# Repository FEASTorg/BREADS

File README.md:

# BREADS

BREADS is the Broadly Expandable and Reconfigurable Data Acquisition and Automation Device Standard.

> You’ve heard of breaking bread — now try building with it!

## Documentation

To see the full documentation visit [our page](https://feastorg.github.io/BREADS/).

## Contributing

Start designing your own slice or make a pull with your improvements!

For more details see the [feastorg CONTRIBUTING](https://github.com/feastorg/.github/blob/main/profile/CONTRIBUTING.md) guidelines on our organization profile.

### Mechanical (Cases)

All case designs can be found on [Onshape](https://cad.onshape.com/documents/f4c13a5c0b1f8d88ed1f5752/w/29d0c0346ddaeb06e16ff42f/e/1077373224ada363d171e3fe?renderMode=0&uiState=65d3aad45b82c32cb51ae4c9)

### Ideas

To see the current wish list for the BREADS family see the [bread ideas](docs/dev_docs/future_slice_ideas.md) doc.

## License

All firmware and software in this repository are licensed under the GNU General Public License v3.0 (GPLv3), and all hardware is licensed under the CERN Open Hardware Licence Version 2 – Strongly Reciprocal (CERN OHL-S v2). These licenses apply specifically to all original designs, technologies, and artwork developed for the BREADS project.

See the relevant [license](./LICENSE) file for full terms, including usage, modification, and redistribution.

## Acknowledgements

[Acknowledge any contributors, collaborators, funding sources, or organizations that supported the project.]

## Contact

[Provide contact information for the project maintainer(s) or lead researcher(s). Include an email address or a link to a contact form.]

---

<div align="center">
  
</div>

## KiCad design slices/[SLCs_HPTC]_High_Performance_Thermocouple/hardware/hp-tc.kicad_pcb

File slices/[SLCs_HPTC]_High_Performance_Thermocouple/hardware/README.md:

# High Performance Thermocouple Amplifier

## Design Goals and Specifications for High-Speed Isolated Thermocouple Project

### Calibration and Temperature Considerations
- Calibration techniques will rely on physical phenomena, like boiling points, but must account for atmospheric pressure variations, as these can affect the boiling points. 
    - Particularly relevant for calibration at different elevations above sea level.
- A proposal to use distilled water for calibration to achieve "close enough" results within a +/-0.1°C margin at a 100°C range was discussed but noted to have limitations based on elevation and atmospheric conditions.
- An alternative calibration method involving triple-point thermal references was suggested for precision but recognized as less accessible.

### Thermocouple and Amplifier Specifications
- The project will initially focus on Type K thermocouples.
- The analog front-end amplifier should have an input-offset less than 4μV. Noise, drift, and linearity, along with not loading the thermocouple, are primary concerns.
- The aim is for the thermocouple to have no more than 10 microamps of loading current, preferably less than 1.5 microamps.
- Microcontroller Unit (MCU) specifications include at least 16KB flash to accommodate future expansions like a Look-Up Table (LUT) for better matching to the exact thermocouple curve.

### Design and Integration
- The discussion covered different approaches to integrating the components, emphasizing the importance of a high input impedance for accurate measurements.
- A digital temperature sensor for ambient temperature measurement at the thermocouple connection point on the board was considered crucial for relative measurements.
- There was a significant focus on selecting the right connectors and ensuring compatibility with different thermocouples, as well as considering built-in cold-compensation sensors.

### Component Selection and Cost Considerations
- Efforts to minimize costs while maintaining performance were evident, with discussions around sourcing components, choosing MCUs with built-in DACs, and finding economical PCB manufacturing options.
- The Bill of Materials (BOM) cost estimation hovered around $25-$30, with additional costs for PCB manufacturing and shipping considered. The aim is to keep the total cost reasonable while enabling scalability in manufacturing.

### Calibration and Output Accuracy
- There were suggestions for making the linear approximation of temperature readings accurate within specific high-temperature ranges (900°C to 1100°C), acknowledging that errors at lower temperatures would be less critical.
- Digital outputs and possibly eliminating analog outputs were discussed to streamline the design and reduce complexity.

### PCB Design and Manufacturing
- Advanced PCB design techniques were considered to accommodate tight space requirements and high-resolution traces, specifically for components like QFN packages with exposed pads.
- The possibility of integrating a designated type K thermocouple socket was discussed, noting its impact on the BOM cost but its importance for compatibility and ease of use.

### Additional Notes
- The team explored various ideas for enhancing the project's design, such as integrating temperature sensors directly on the PCB for more accurate cold-junction compensation and discussing the practical aspects of assembling small components without professional equipment.
- There was a continuous emphasis on balancing performance, cost, and usability to ensure that the final product would be accessible and useful to a broad audience.

## Technical Dissemination

### 1. Power Supply and Isolation

#### Components:
- **U3 (H11L1)**: Optocoupler
- **U4, U5 (AP2112K-3.3)**:  3.3V low dropout regulators. Provide isolated stable voltage for the circuit.
- **D1 (Schottky Diode)**: Reverse polarity protection.
- **L1 (Coupled Inductor)**: Provides isolation and filtering for the power supply.
- **C1, C2, C3, C4, C5, C6, C7, C8, C9, C10, C11, C12**: Capacitors for filtering and decoupling.
- **D2 (Zener Diode)**: Overvoltage protection.
- **R1, R2, R3, R4**: Current limiting and voltage division resistors.

### 2. Thermocouple Input and Amplification

#### Components:
- **U6A (IS1221)**: Instrumentation amplifier for thermocouple signal amplification.
- **R5, R6, R7**: Precision resistors for setting amplifier gain.
- **C13, C14, C15, C16, C17, C18, C19**: Filtering capacitors.
- **R8 (Trim-Pot)**: Adjustable resistor for fine-tuning gain.

### 3. Analog-to-Digital Conversion

#### Components:
- **U7 (MCP1501T-20E)**: Precision voltage reference.
- **U2 (MCP3565R)**: High-resolution ADC.
- **C20, C21, C22, C23, C24, C25, C26, C27, C28, C29, C30**: Decoupling and filtering capacitors.
- **R9, R10, R11, R12, R13, R14, R15, R16, R17**: Resistors for setting input impedance and filtering.

### 4. Microcontroller and Interface

### Components:
- **U1 (MSPM0G1507SPTR)**: Microcontroller for processing digital signals and handling communication.
- **C31, C32, C33, C34, C35, C36**: Decoupling capacitors for MCU power supply.
- **R18, R19, R20**: Resistors for setting up MCU I/O lines.

### 5. Temperature Sensor for Cold-Junction Compensation

#### Components:
- **U10 (TMP112)**: Digital temperature sensor.
- **R21, R22**: Pull-up resistors for I2C lines.
- **C37, C38**: Decoupling capacitors.

### 6. Isolation and Data Communication

#### Components:
- **ISO-MISO, ISO-MOSI**: Isolated SPI lines.
- **ISO6721RB**: Digital isolator.
- **C39, C40, C41**: Filtering capacitors.

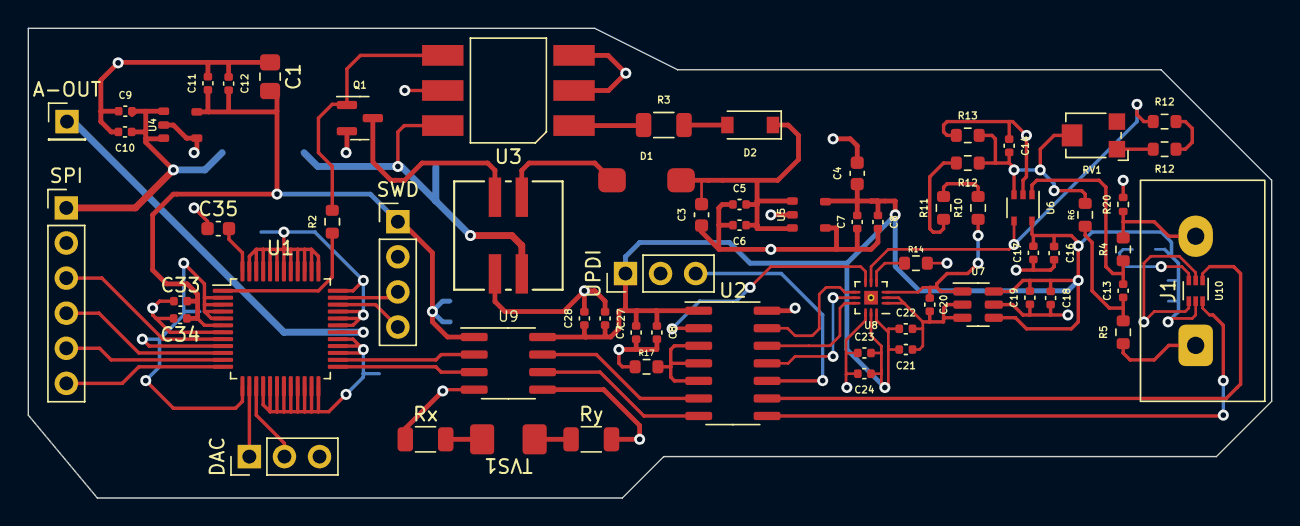
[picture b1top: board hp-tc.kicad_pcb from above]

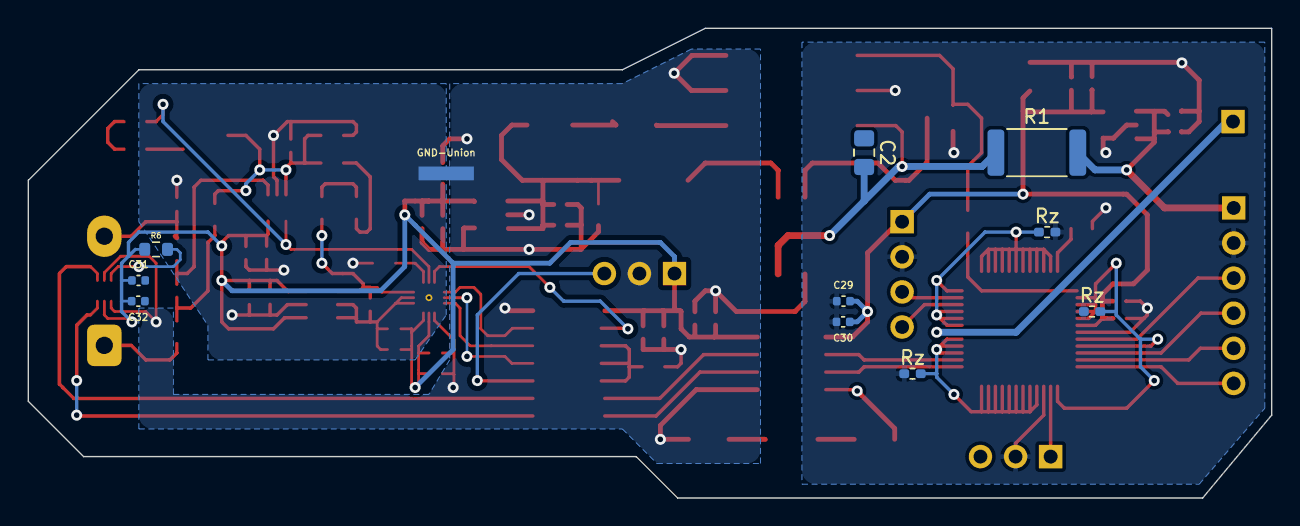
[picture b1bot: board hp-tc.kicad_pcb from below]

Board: 2 copper layers, 90.0 x 34.0 mm, 78 parts (11 on the bottom side), 4 nets.

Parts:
A-OUT: PinHeader_1x01_P2.54mm_Vertical
C1, C2: C_0805_2012Metric_Pad1.18x1.45mm_HandSolder
C3, C4: 2u2; C_0603_1608Metric
C5, C7, C7#2, C9, C11, C14, C16, C18, C20, C21, C23, C27, C29, C31, C33: 1u; C_0402_1005Metric
C6, C8, C8#2, C10, C12, C17, C19, C22, C24, C28, C30, C32, C34: 10n; C_0402_1005Metric
C13: 0u1; C_0402_1005Metric
C35: 0u47; C_0603_1608Metric
D1: SK14
D2: 3v; D_SOD-123
DAC: PinHeader_1x03_P2.54mm_Vertical
GND-Union: GND-Union
J1: TypeKSocket
L1: SRF0703-6R8M; IND_SRF0703-101M_BRN-M
Q1: DMN2310U; SOT-23
R1: 4R7; R_2512_6332Metric
R2: 1K; R_0603_1608Metric
R3: 10; R_1206_3216Metric
R4, R5, R10, R11, R12, R13: 1k; R_0603_1608Metric
R6, R6#2, R14, R17: 22k; R_0603_1608Metric
R12#2: 47k; R_0603_1608Metric
R12#3: 470k; R_0603_1608Metric
R20: 10M; R_0402_1005Metric
RV1: 20k; Potentiometer_Bourns_TC33X_Vertical
Rx: R_1206_3216Metric
Ry: R_1206_3216Metric
Rz: 1M; R_0402_1005Metric_Pad0.72x0.64mm_HandSolder
Rz#2, Rz#3: 1M; R_0402_1005Metric_Pad0.72x0.64mm_HandSolder
SPI: PinHeader_1x06_P2.54mm_Vertical
SWD: PinHeader_1x04_P2.54mm_Vertical
TVS1: DO-214AA
U1: MSPM0G1507SPTR; LQFP-48_7x7mm_P0.5mm
U2: ATtiny1604; SOIC-14_3.9x8.7mm_P1.27mm
U3: H11L1; H11L1-4
U4, U5: SOT25
U6: TSZ121; SOT-353_SC-70-5
U7: MCP1501; SOT-23-6
U8: MCP3565
U9: ISO6721RFBDR; SOIC-8_3.9x4.9mm_P1.27mm
U10: TMP112; SOT-563
UPDI: PinHeader_1x03_P2.54mm_Vertical

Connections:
GND1: C1.1, C9.1, C10.2, C11.2, C12.1, C29.1, C30.2, C33.1, C34.2, C35.1, DAC.2, Q1.2, Rz.1, Rz#2.1, Rz#3.2, SPI.2, SWD.2, U1.7, U3.5, U4.2, U4.4
GND2: C3.1, C4.2, C5.1, C6.2, C7.1, C7#2.1, C8.2, C8#2.2, C23.1, C24.2, C27.1, C28.2, C31.2, C32.1, GND-Union.1, L1.4, R17.1, Ry.2, U2.14, U3.2, U3.3, U5.2, U5.4, U8.10, U9.5, U10.2, U10.4, UPDI.2
GNDA: C14.1, C16.2, C17.1, C18.2, C19.1, C20.2, C21.1, C22.2, GND-Union.2, R13.1, R14.2, R20.2, U6.2, U7.2, U7.3, U7.5, U8.1, U8.2, U8.13
UPDI: U2.10, UPDI.3

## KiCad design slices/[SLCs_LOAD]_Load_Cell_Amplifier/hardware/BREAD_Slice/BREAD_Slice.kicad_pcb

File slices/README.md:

# slices

## Directory Contents

- Management
  - [LOAFm_ESPTP_ESP32_Thing_Plus_Controller](./[LOAFm_ESPTP]_ESP32_Thing_Plus_Controller/README.md)
  - [LOAFm_x04_LOAF_Backplane_Extender_x04](./[LOAFm_x04]_LOAF_Backplane_Extender_x04/README.md)
- Actuation
  - [SLCa_SERV_Servo_Motor_Controller](./[SLCa_SERV]_Servo_Motor_Controller/README.md)
  - [SLCa_STEP_Stepper_Motor_Controller](./[SLCa_STEP]_Stepper_Motor_Controller/README.md)
  - [SLCa_DCMT_DC_Motor_Controller](./[SLCa_DCMT]_DC_Motor_Controller/README.md)
  - [SLCa_PUMP_Pump_Controller](./[SLCa_PUMP]_Pump_Controller/README.md)
  - [SLCa_RLAY_4_Channel_Relay](./[SLCa_RLAY]_4_Channel_Relay/README.md)
  - [SLCa_DC_Motor_Discrete_HBridge](./[SLCa_DCMT]_DC_Motor_Discrete_HBridge/README.md) **New**
- Communication
  - [SLCc_USBP_USB_Port](./[SLCc_USBP]_USB_Port/README.md)
- Integrated
  - [SLCi_HEAT_Heating_Element_Controller](./[SLCi_HEAT]_Heating_Element_Controller/README.md)
  - [SLCi_RLHT_Relay_Heating_Element_Controller](./[SLCi_RLHT]_Relay_Heating_Element_Controller/README.md)
- Power
  - [SLCp_BUCK_Buck_Converter_Signal_Generator](./[SLCp_BUCK]_Buck_Converter_Signal_Generator/README.md)
  - [SLCp_SOLR_Field_Solar_Power](./[SLCp_SOLR]_Field_Solar_Power/README.md)
- Sensing
  - [SLCs_CR40_40A_Current_Sensor](./[SLCs_CR40]_40A_Current_Sensor/README.md)
  - [SLCs_CR20_20A_Current_Sensor](./[SLCs_CR20]_20A_Current_Sensor/README.md)
  - [SLCs_CR10_10A_Current_Sensor](./[SLCs_CR10]_10A_Current_Sensor/README.md)
  - [SLCs_LVAI_Analog_Reader](./[SLCs_LVAI]_Analog_Reader/README.md)
  - [SLCs_AAFT_Audio_Analysis](./[SLCs_AAFT]_Audio_Analysis/README.md)
  - [SLCs_THRM_Thermocouple_Reader](./[SLCs_THRM]_Thermocouple_Reader/README.md)
  - [SLCs_PHDO_pH_Dissolved_Oxygen_Sensor](./[SLCs_PHDO]_pH_Dissolved_Oxygen_Sensor/README.md)
  - [SLCs_PDER_pH_DO_EC_RP_Sensor](./[SLCs_PDER]_pH_DO_EC_RP_Sensor/README.md) **New**
  - [SLCs_HPTC_High_Performance_Thermocouple](./[SLCs_HPTC]_High_Performance_Thermocouple/README.md) **New**
  - [SLCs_LOAD_Load_Cell_Amplifier](./[SLCs_LOAD]_Load_Cell_Amplifier/README.md) **New**
- Template
  - [SLCx_TEMP_Template](./[SLCx_TEMP]_Template/README.md)

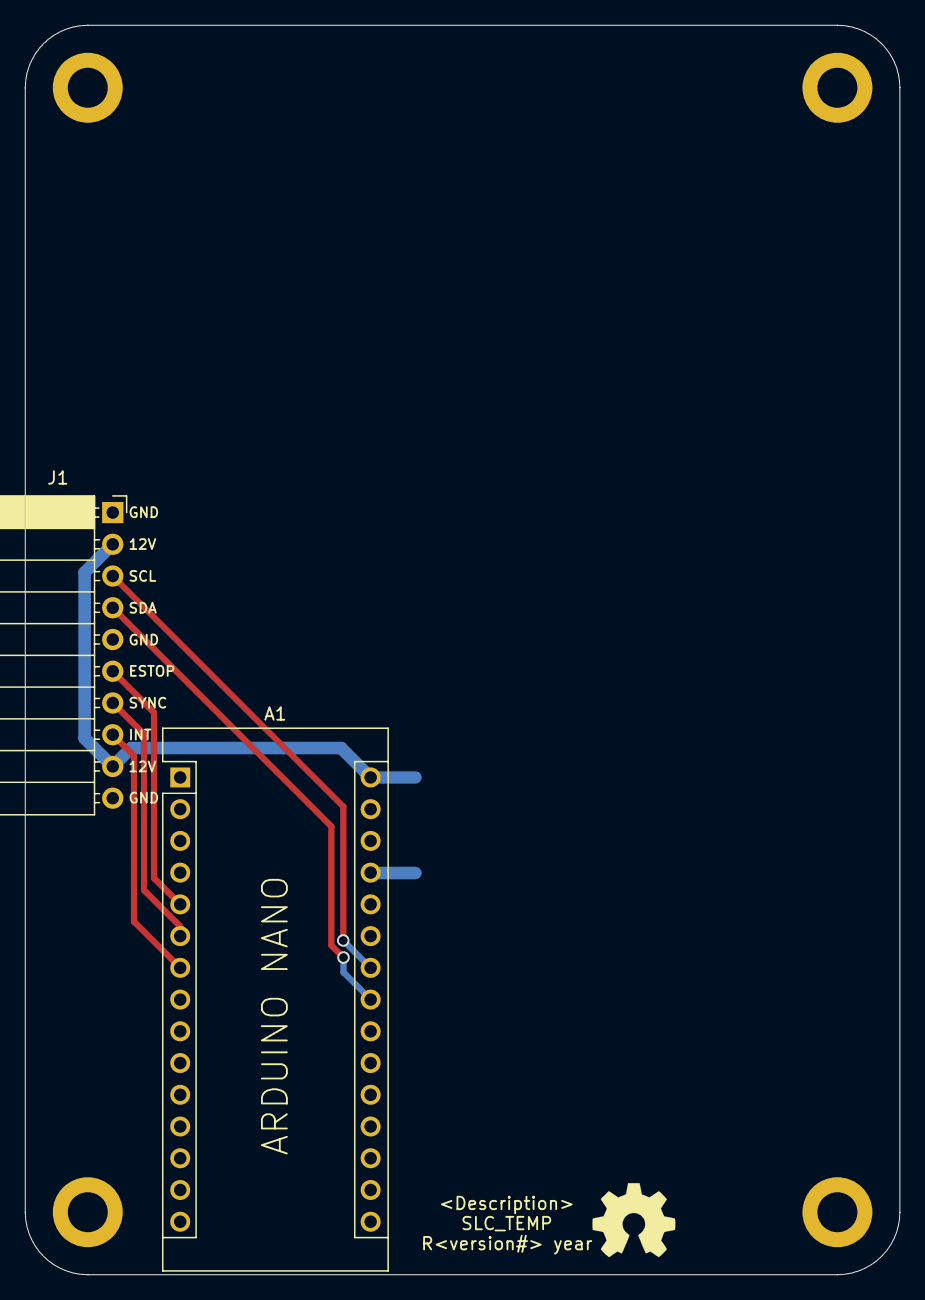
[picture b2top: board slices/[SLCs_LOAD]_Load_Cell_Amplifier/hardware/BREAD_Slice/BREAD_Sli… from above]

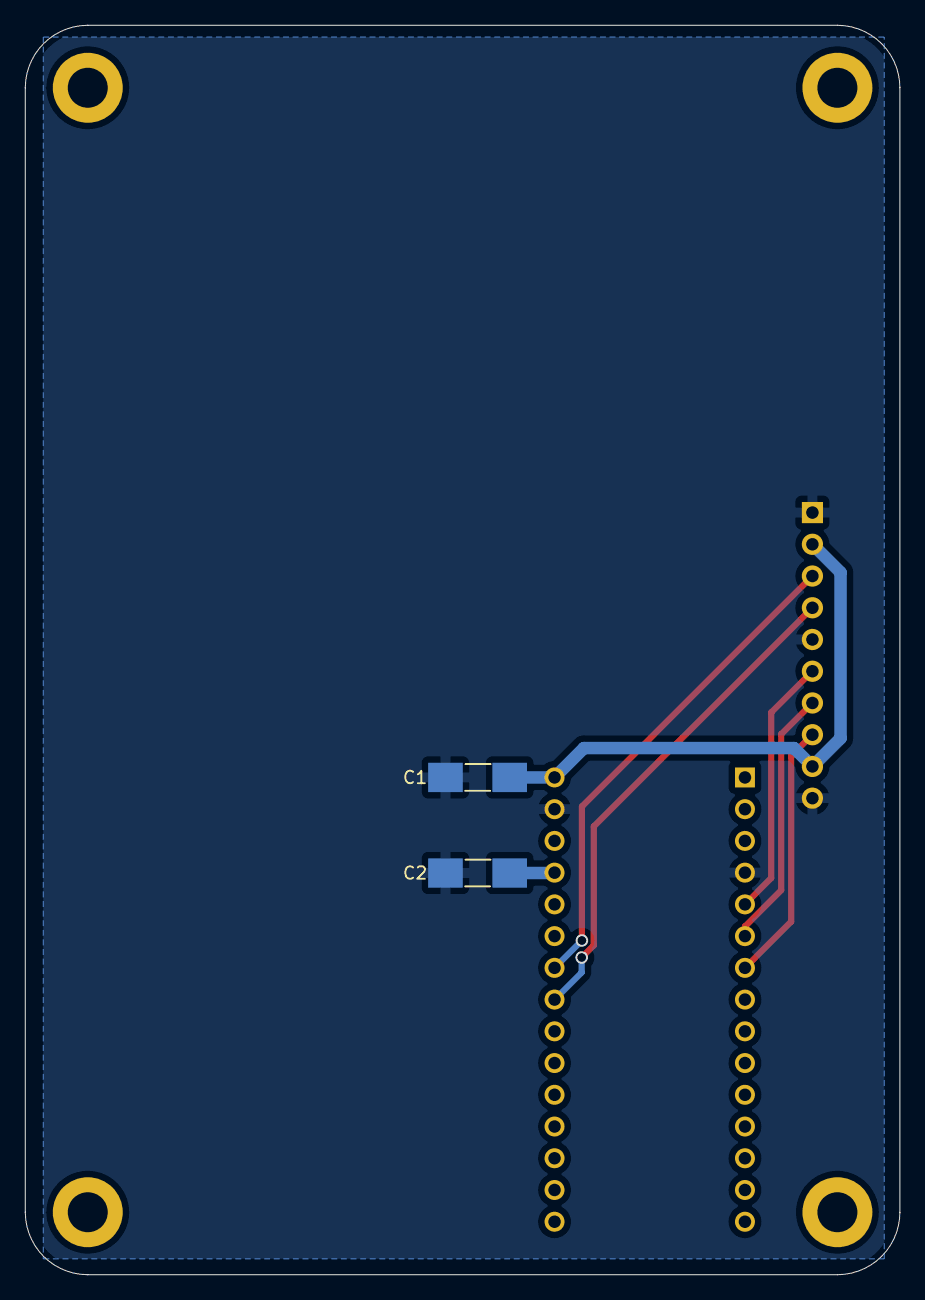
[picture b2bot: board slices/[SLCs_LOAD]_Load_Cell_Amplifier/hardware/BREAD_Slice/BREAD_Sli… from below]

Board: 2 copper layers, 70.0 x 100.0 mm, 9 parts (2 on the bottom side), 8 nets.

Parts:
A1: Arduino_Nano_v3.x; Arduino_Nano
C1, C2: 10uF_t; C_2312
H1, H2, H3, H4: MountingHole; MountingHole_3.2mm_M3_DIN965_Pad
J1: Conn_01x10_Female; PinSocket_1x10_P2.54mm_Horizontal
Logo1: Logo_Open_Hardware_Small; OSHW-Symbol_6.7x6mm_SilkScreen

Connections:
+5V: A1.27 (+5V), C2.1
+12V: A1.30 (VIN), C1.1, J1.2, J1.9
/E_STOP: A1.5 (D2), J1.6
/I2C_CLK: A1.24 (A5), J1.3
/I2C_DAT: A1.23 (A4), J1.4
/INT: A1.6 (D3), J1.7
/SYNC: A1.7 (D4), J1.8
GND: A1.4 (GND), A1.29 (GND), C1.2, C2.2, J1.1, J1.5, J1.10

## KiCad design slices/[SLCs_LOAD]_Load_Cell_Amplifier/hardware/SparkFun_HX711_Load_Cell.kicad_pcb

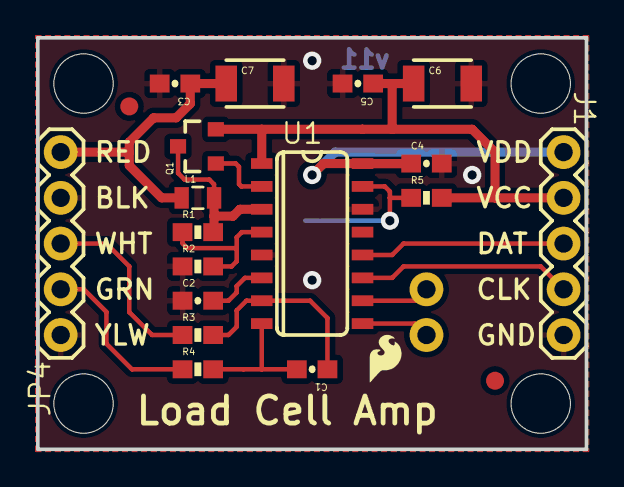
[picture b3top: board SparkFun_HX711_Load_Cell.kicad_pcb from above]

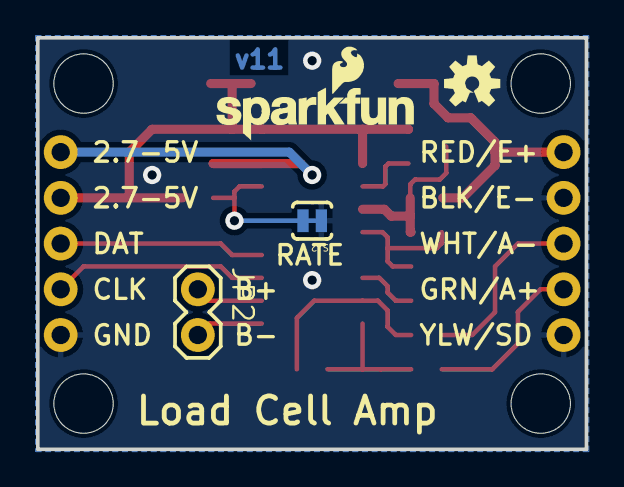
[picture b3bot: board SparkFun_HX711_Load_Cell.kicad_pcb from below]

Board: 2 copper layers, 30.5 x 22.9 mm, 30 parts (4 on the bottom side), 17 nets.

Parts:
C1, C2, C3, C4, C5: 0.1uF; 0603-CAP
C6, C7: 10uF; 1210
FID1, FID2: FIDUCIAL1X2; FIDUCIAL-1X2
FRAME1: FRAME-LETTER; CREATIVE_COMMONS
J1: 1X05
JP2: 1X02
JP4: 1X05
L1: 3.3uH; 0805
LOGO1: SFE_LOGO_NAME_FLAME.1_INCH; SFE_LOGO_NAME_FLAME_.1
LOGO3: SFE_LOGO_FLAME.1_INCH; SFE_LOGO_FLAME_.1
Q1: MMBT4403; SOT23-3
R1: 20k; 0603-RES
R2: 8.2K; 0603-RES
R3, R4: 100; 0603-RES
R5: 10K; 0603-RES
SJ2: PAD-JUMPER-2-NC_BY_TRACE_YES_SILK
STANDOFF1, STANDOFF2, STANDOFF3, STANDOFF4: STAND-OFF
U1: HX711; SO16
U7: OSHW-LOGOS; OSHW-LOGO-S
U$1: REVISION

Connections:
A+: JP4.2, R4.1
A-: JP4.3, R3.1
AVDD: C3.1, C7.1, JP4.5, L1.1
B+: JP2.1, U1.10
B-: JP2.2, U1.9
DAT: J1.3, U1.12
GND: C2.1, C3.2, C4.2, C5.2, C6.2, C7.2, J1.5, JP4.1, JP4.4, R2.1, SJ2.1, U1.5, U1.14
unnamed: R5.1, SJ2.2, U1.15
unnamed: C1.1, R3.2, U1.7
unnamed: C1.2, R4.2, U1.8
unnamed: Q1.1, U1.2
unnamed: L1.2, Q1.3, R1.2, U1.3
unnamed: R1.1, R2.2, U1.4
unnamed: C2.2, U1.6
SCK: J1.4, U1.11
VCC: C5.1, C6.1, J1.2, Q1.2, R5.2, U1.1
VDD: C4.1, J1.1, U1.16

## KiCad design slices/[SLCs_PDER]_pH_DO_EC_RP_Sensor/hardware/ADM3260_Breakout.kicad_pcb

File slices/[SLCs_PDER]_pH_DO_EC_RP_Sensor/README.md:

# PDER

## Overview

Carrier for the Atlas OEM sensor boards for potential of hydrogen (pH), dissolved oxygen (DO), electrical conductivity (EC), and oxidation reduction potential (ORP).

This design builds off of:
* [github.com/skullbox305/Atlas-Scientific-pH-OEM-ADM3260](https://github.com/skullbox305/Atlas-Scientific-pH-OEM-ADM3260). 
* Eagle PCB Design for Atlas Scientific OEM pH and ORP Sensors. Noise Isolation with ADM3260

## Engineering Notepad

### Schematic Overview

The schematic contains several key components and sections:

1. **I2C Isolation (U1 - ADM3260)**
   - **Purpose**: The ADM3260 is a signal and power isolated I2C digital isolator with a voltage regulator.
   - **Connections**:
     - **Primary Side (SCL2, SDA2)**: These lines connect to the I2C bus of the non-isolated side.
     - **Secondary Side (SCL1, SDA1)**: These lines connect to the isolated I2C bus.
     - **Power**: The chip is powered by AVCC on the primary side and 3.3V-ISO on the secondary side. Capacitors (C1-C8) are used for decoupling.

2. **CMOS Power Switch (Q1, Q2, Q3)**
   - **Purpose**: Controls the power to the isolated section.
   - **Connections**: 
     - **EN**: The enable line controls the gates of the MOSFETs, allowing the AVCC power to be switched.

3. **Analog Sensor (U2)**
   - **Purpose**: This interfaces with an Atlas Scientific OEM module sensor.
   - **Connections**: 
     - **SDA, SCL**: Connected to the isolated I2C bus.
     - **VCC, GND**: Power connections.
     - **PRB, PRBGND**: Probe connections.

### Layer Arrangement

The arrangement of layers is crucial for signal integrity, power distribution, and minimizing noise:

1. **Top Layer (Signal Layer)**:
   - Contains components and critical signal traces.
   - Provides easy access for soldering and modifications.

2. **Inner Layers (Power and Ground Planes)**:
   - **Inner Layer 1 (Yellow)**: Dedicated to power (e.g., 3.3V, 5V), providing a stable power distribution network.
   - **Inner Layer 2 (Green)**: Dedicated to ground (GND), reducing the loop area for ground currents and minimizing EMI.

3. **Bottom Layer (Signal Layer)**:
   - Used for additional routing if the top layer is congested.
   - Can also contain components, though it’s often less populated than the top layer.

### Key Clarifications

- **I2C Isolation**: The ADM3260 ensures that the I2C bus on the primary side is electrically isolated from the secondary side. This prevents noise and interference from affecting sensitive analog measurements.
- **Power Switch**: The CMOS power switch ensures that the isolated section can be powered down independently, reducing power consumption when the sensor is not in use.
- **Ground and Power Planes**: The use of dedicated ground and power planes reduces noise and provides a stable reference for all signals, improving overall performance and reliability.

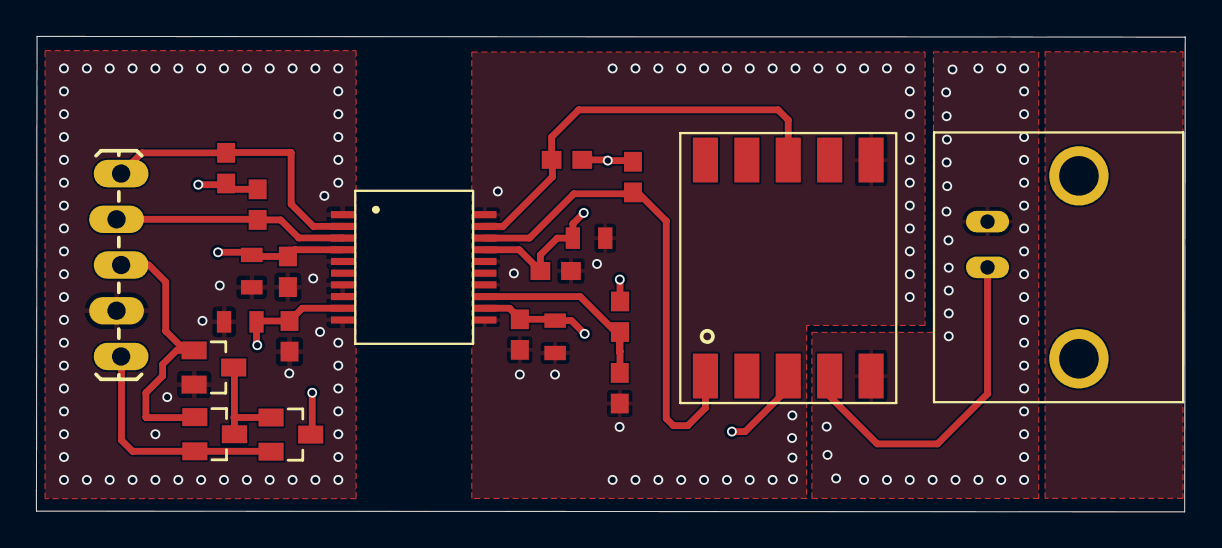
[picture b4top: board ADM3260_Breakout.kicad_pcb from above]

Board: 4 copper layers, 63.8 x 26.4 mm, 21 parts (0 on the bottom side), 14 nets.

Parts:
C1, C3, C6, C8: 10uF; 0805
C2, C4, C5, C7: 0.1uF; 0603
J1: 1X05_LOCK_LONGPADS
J2: BNCPTH; BNC
Q1, Q3: PMV32UP; SOT23
Q2: PMV16XN; SOT23
R1, R2, R3, R4: 4.7k; 0603
R5: 16.2k; 0603
R6: 10k; 0603
U1: ADM3260
U2: Atlas Scientific OEM pH or ORP; PHSENSOR

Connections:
3V3-ISO: C5.1, C6.1, C7.1, C8.1, R3.2, R4.2, R5.2, U1.P$12, U1.P$17, U2.P$3
AVCC: C1.1, C2.1, C3.1, C4.1, Q3.3, R1.2, R2.2, U1.P$4, U1.P$9
EN: J1.3, Q1.1, Q2.1
GND: C1.2, C2.2, C3.2, C4.2, J1.4, Q2.2, U1.P$1, U1.P$5, U1.P$7, U1.P$8, U1.P$10
GND-ISO: C5.2, C6.2, C7.2, C8.2, R6.1, U1.P$11, U1.P$14, U1.P$16, U1.P$20, U2.P$6
unnamed: R5.1, R6.2, U1.P$13
unnamed: Q1.3, Q2.3, Q3.1
PRB: J2.S, U2.P$4
PRBGND: J2.GND, U2.P$5
SCL1: R4.1, U1.P$19, U2.P$8
SCL2: J1.1, R1.1, U1.P$2
SDA1: R3.1, U1.P$18, U2.P$1
SDA2: J1.2, R2.1, U1.P$3
VCC: J1.5, Q1.2, Q3.2

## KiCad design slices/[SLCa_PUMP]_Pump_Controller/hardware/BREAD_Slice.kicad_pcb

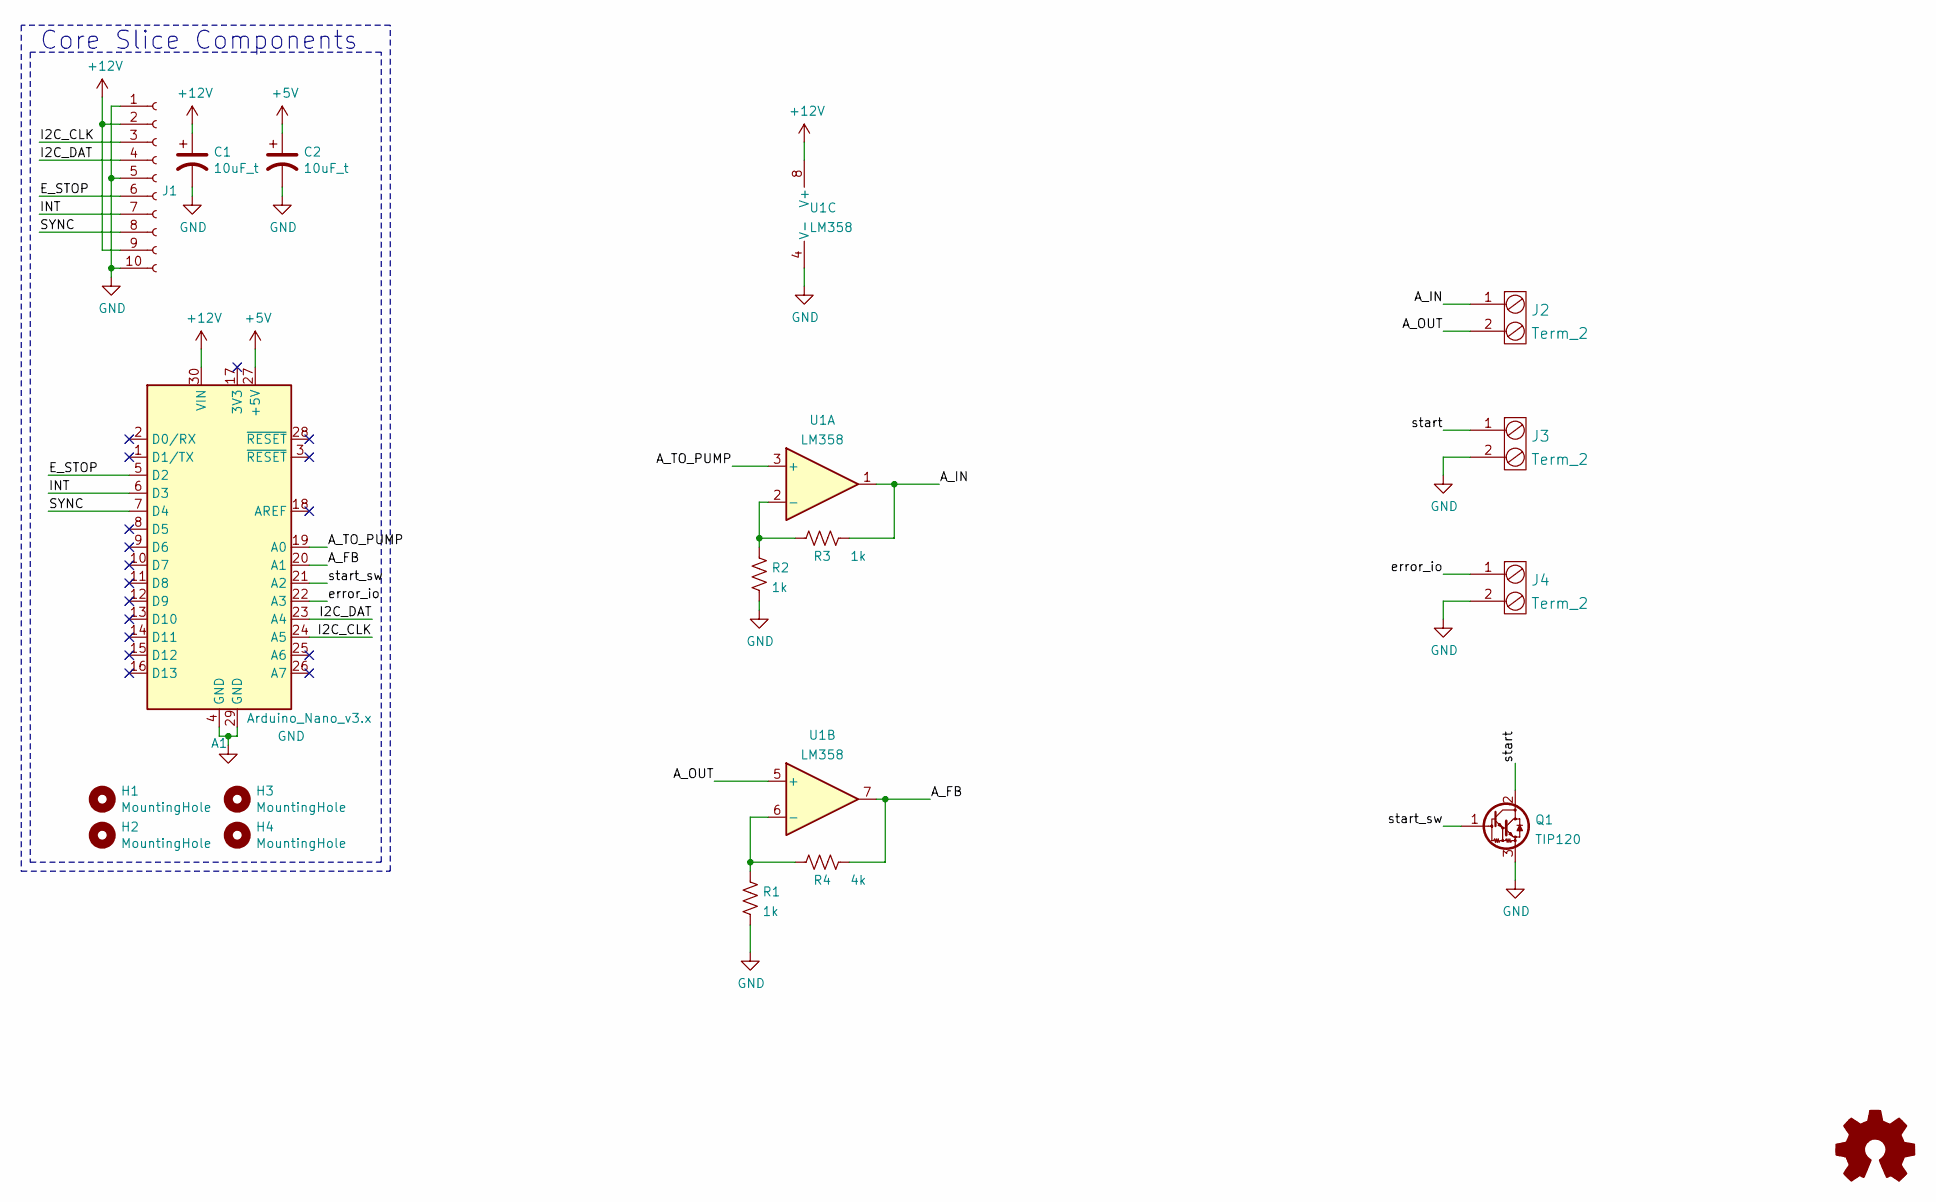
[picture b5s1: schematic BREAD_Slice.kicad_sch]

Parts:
A1: Arduino_Nano_v3.x; Arduino_Nano
C1, C2: 10uF_t; C_2312; Part # T491C106K025AT
H1, H2, H3, H4: MountingHole; MountingHole_3.2mm_M3_DIN965_Pad
J1: Conn_01x10_Female; PinSocket_1x10_P2.54mm_Horizontal
J2, J3, J4: Term_2; TerminalBlock_Pheonix_MKDS1.5-2pol; Part # 1935161
Logo1: Logo_Open_Hardware_Small; OSHW-Symbol_6.7x6mm_SilkScreen
Q1: TIP120; TO-220-3_Vertical
R1, R2, R3: 1k; R_1206_HandSoldering
R4: 4k; R_1206_HandSoldering
U1: LM358; DIP-8_W7.62mm_LongPads

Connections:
+5V: A1.27 (+5V), C2.1
+12V: A1.30 (VIN), C1.1, J1.2, J1.9, U1.8 (V+)
/A_FB: A1.20 (A1), R4.2, U1.7
/A_IN: J2.1, R3.2, U1.1
/A_OUT: J2.2, U1.5 (+)
/A_TO_PUMP: A1.19 (A0), U1.3 (+)
/E_STOP: A1.5 (D2), J1.6
/I2C_CLK: A1.24 (A5), J1.3
/I2C_DAT: A1.23 (A4), J1.4
/INT: A1.6 (D3), J1.7
/SYNC: A1.7 (D4), J1.8
/error_io: A1.22 (A3), J4.1
/start: J3.1, Q1.2 (C)
/start_sw: A1.21 (A2), Q1.1 (B)
GND: A1.4 (GND), A1.29 (GND), C1.2, C2.2, J1.1, J1.5, J1.10, J3.2, J4.2, Q1.3 (E), R1.1, R2.1, U1.4 (V-)
unnamed: R1.2, R4.1, U1.6 (-)
unnamed: R2.2, R3.1, U1.2 (-)

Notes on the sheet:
Core Slice Components

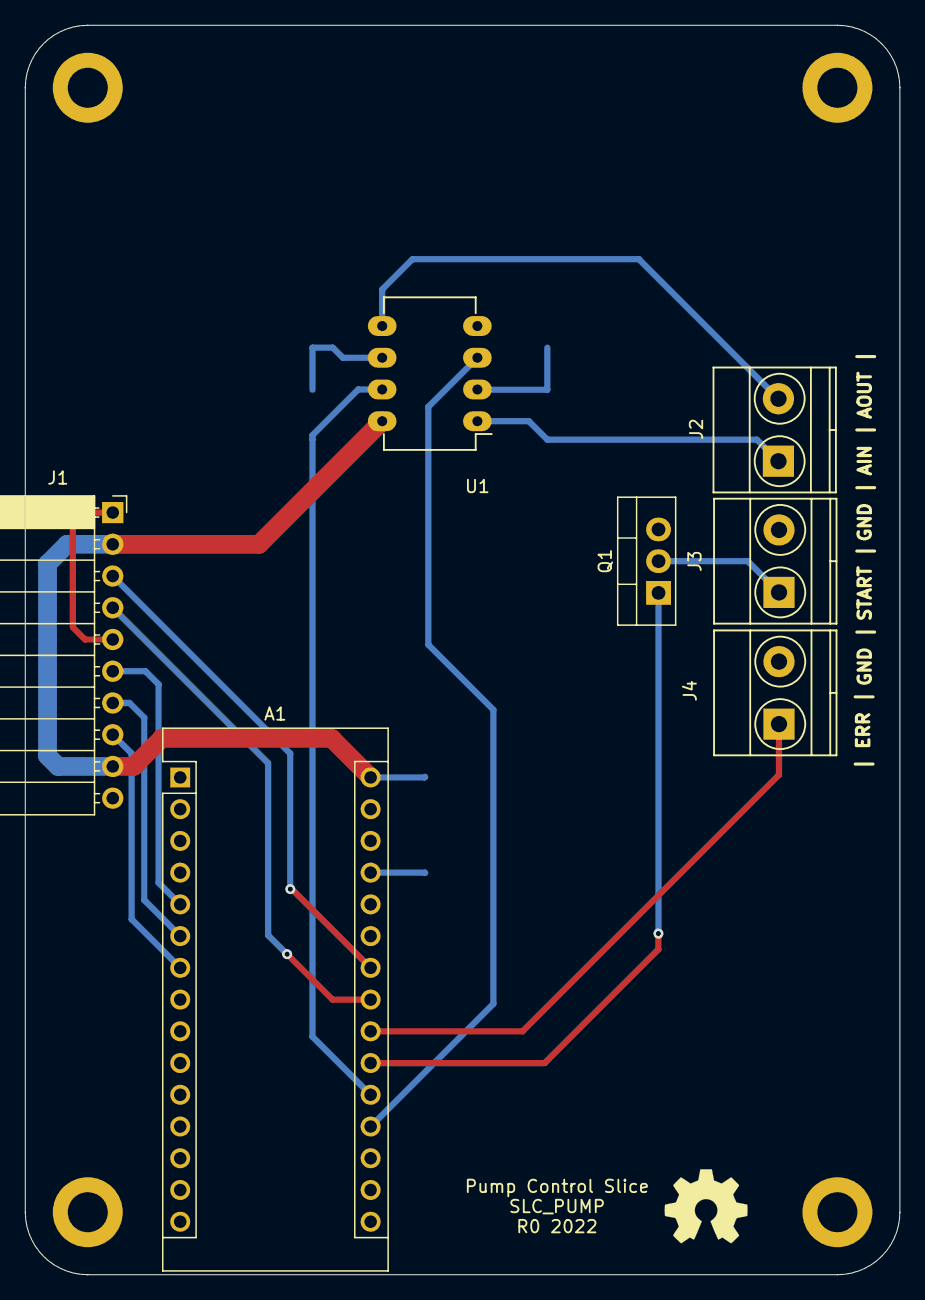
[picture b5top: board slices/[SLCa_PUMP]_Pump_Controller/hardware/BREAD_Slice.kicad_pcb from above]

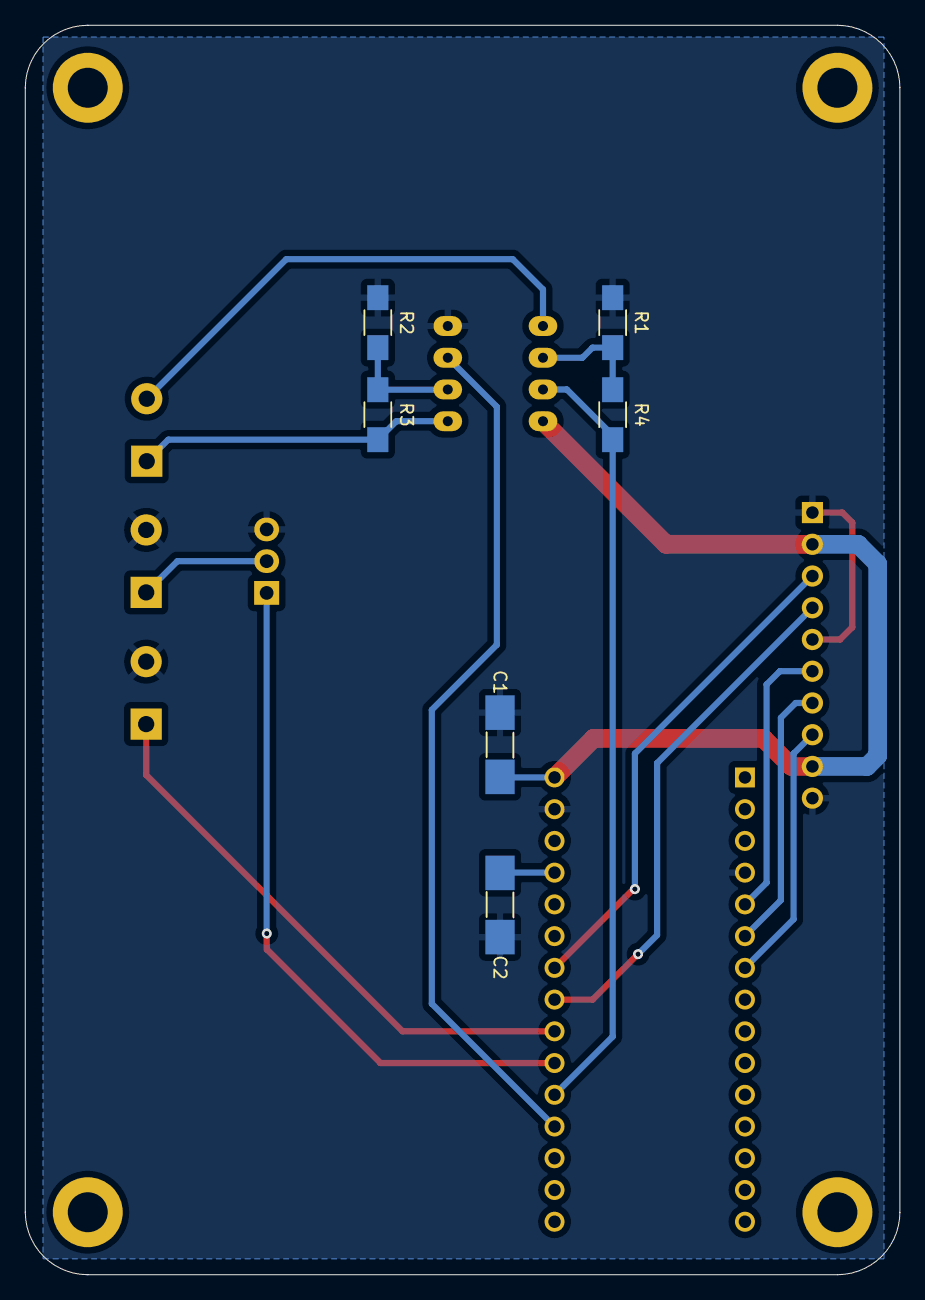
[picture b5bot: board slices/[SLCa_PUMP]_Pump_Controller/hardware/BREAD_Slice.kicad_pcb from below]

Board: 2 copper layers, 70.0 x 100.0 mm, 18 parts (6 on the bottom side), 17 nets.

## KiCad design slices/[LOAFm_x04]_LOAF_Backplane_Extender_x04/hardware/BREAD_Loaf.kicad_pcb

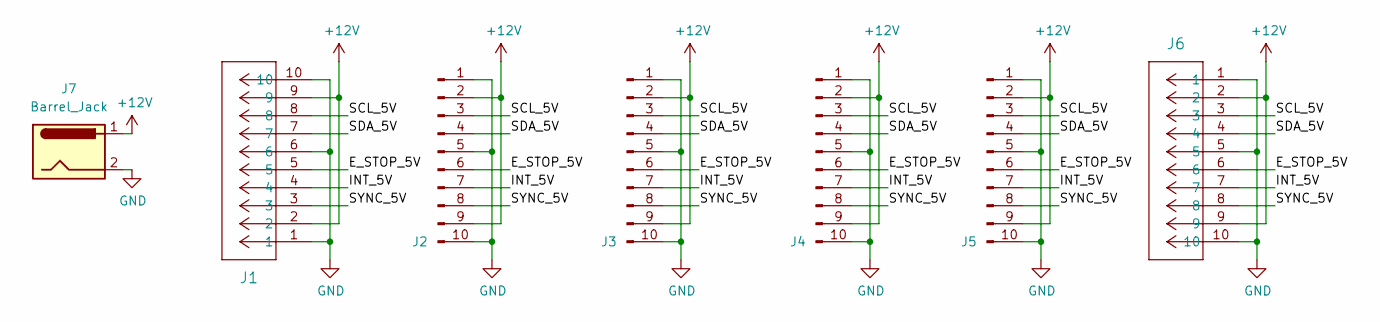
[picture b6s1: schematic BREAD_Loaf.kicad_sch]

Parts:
J1: PPPC101LGBN-RC; 1x10 RA Male Header 2.54mm Pitch
J2, J3, J4, J5: Conn_01x10_Male; BREAD 10-Pin Connector
J6: PPPC101LGBN-RC; PinSocket_1x10_P2.54mm_Horizontal
J7: Barrel_Jack; BarrelJack_CUI_PJ-063AH_Horizontal

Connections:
+12V: J1.2, J1.9, J2.2, J2.9, J3.2, J3.9, J4.2, J4.9, J5.2, J5.9, J6.2, J6.9, J7.1
/E_STOP_5V: J1.5, J2.6, J3.6, J4.6, J5.6, J6.6
/INT_5V: J1.4, J2.7, J3.7, J4.7, J5.7, J6.7
/SCL_5V: J1.8, J2.3, J3.3, J4.3, J5.3, J6.3
/SDA_5V: J1.7, J2.4, J3.4, J4.4, J5.4, J6.4
/SYNC_5V: J1.3, J2.8, J3.8, J4.8, J5.8, J6.8
GND: J1.1, J1.6, J1.10, J2.1, J2.5, J2.10, J3.1, J3.5, J3.10, J4.1, J4.5, J4.10, J5.1, J5.5, J5.10, J6.1, J6.5, J6.10, J7.2

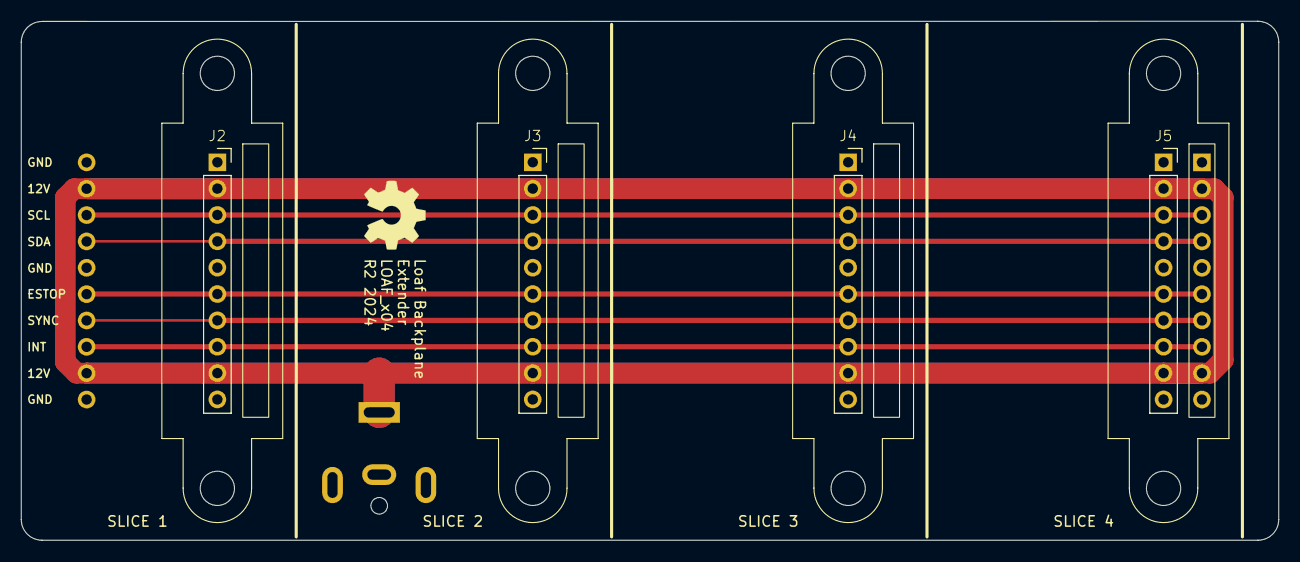
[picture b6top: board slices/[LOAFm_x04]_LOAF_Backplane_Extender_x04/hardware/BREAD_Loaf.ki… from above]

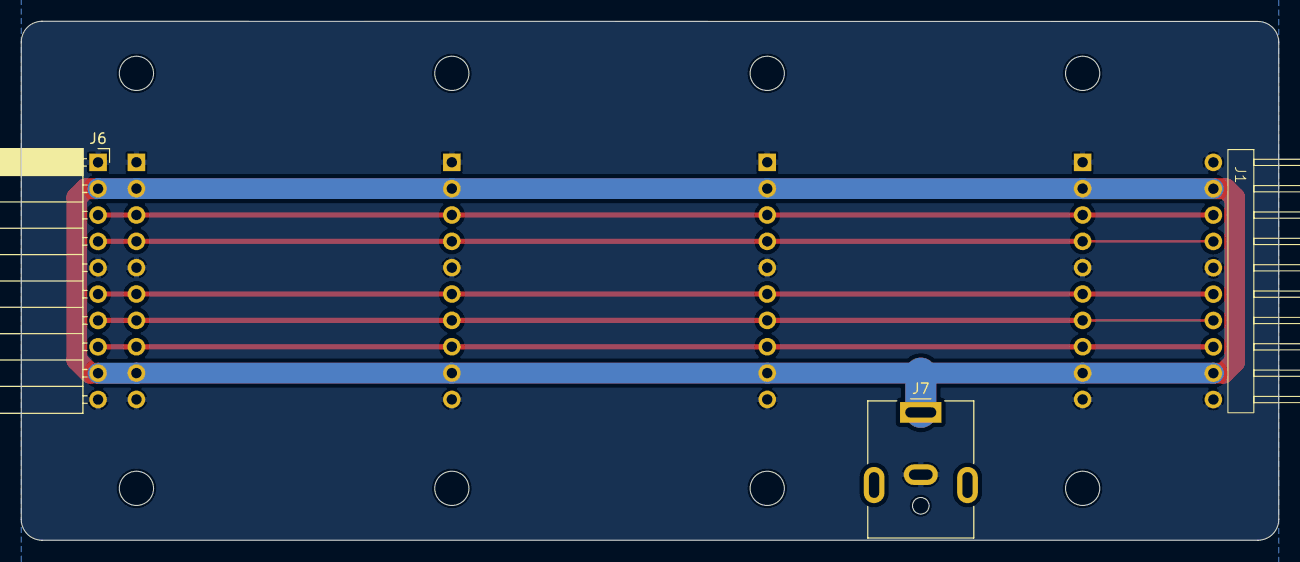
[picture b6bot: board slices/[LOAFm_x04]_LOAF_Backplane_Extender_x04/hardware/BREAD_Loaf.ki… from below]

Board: 2 copper layers, 121.2 x 50.0 mm, 8 parts (3 on the bottom side), 7 nets.

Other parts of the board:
Logo1: Logo_Open_Hardware_Small; OSHW-Symbol_6.7x6mm_SilkScreen

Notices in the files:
parts and their libraries:
Released under the Creative Commons Attribution Share-Alike 4.0 License
https://creativecommons.org/licenses/by-sa/4.0
